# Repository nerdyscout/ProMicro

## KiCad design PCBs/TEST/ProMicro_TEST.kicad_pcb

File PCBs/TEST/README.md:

# ProMicro_TEST
This module can be mounted to an [Arduino Pro Mini](https://www.sparkfun.com/products/11113), [Arduino Nano](https://store.arduino.cc/arduino-nano), [Sparkfun Pro Micro](https://www.sparkfun.com/products/12587), or any other pincompatible MCU running with 3.3V.

## Documentation
All files can be found on [Github](https://github.com/nerdyscout/ProMicro_TEST).

### Schematic

### Layout

### BoM
  * [interactiveHTMLBoM](https://nerdyscout.github.io/ProMicro_TEST/docs/BOM/ProMicro_TEST.html)
  * [kicost](docs/BOM/ProMicro_TEST.xlsx)
  * [csv](docs/BOM/ProMicro_TEST.csv)

## Gerbers
can be found within the Github [repository](https://github.com/nerdyscout/ProMicro_TEST/tree/master/gerbers).

## Code
| | TEST1 | TEST2 |
| --- | --- | --- |
| Arduino Nano | tbd | [TEST](examples/Arduino_Nano_TEST/Arduino_Nano_TEST.ino) |
| Sparkfun ProMicro | [TEST](examples/Sparkfun_ProMicro_TEST/Sparkfun_ProMicro_TEST.ino) | [TEST](examples/Sparkfun_ProMicro_TEST/Sparkfun_ProMicro_TEST.ino) |

## Links
  * [hackaday.io](https://hackaday.io/project/171898-promicro)

## License
Copyright Stefan Herold 2020

This documentation describes Open Hardware and is licensed under the CERN OHL v.1.2.

You may redistribute and modify this documentation under the terms of the CERN OHL v.1.2. (http://ohwr.org/cernohl). This documentation is distributed WITHOUT ANY EXPRESS OR IMPLIED WARRANTY, INCLUDING OF MERCHANTABILITY, SATISFACTORY QUALITY AND FITNESS FOR A PARTICULAR PURPOSE. Please see the CERN OHL v.1.2 for applicable conditions

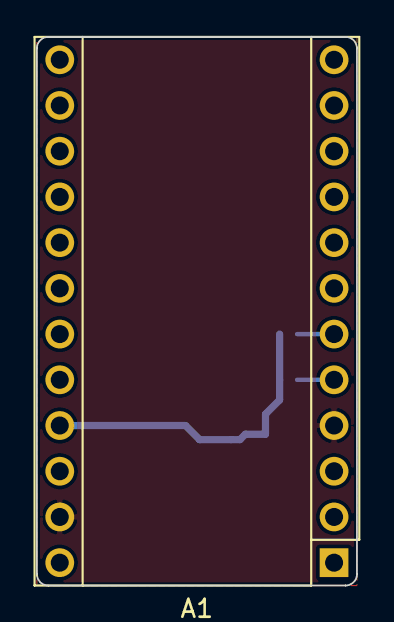
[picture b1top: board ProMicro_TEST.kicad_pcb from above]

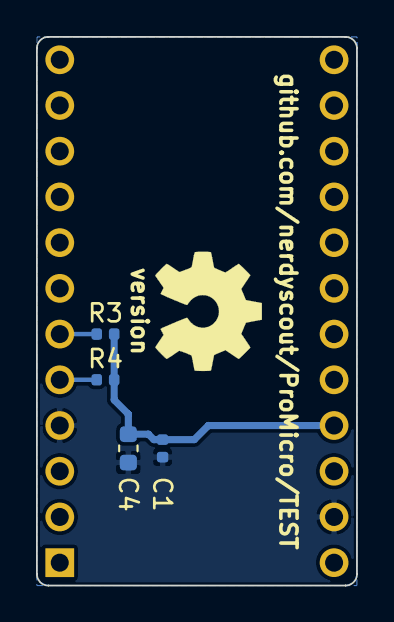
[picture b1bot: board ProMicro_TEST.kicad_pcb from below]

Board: 2 copper layers, 17.8 x 30.5 mm, 6 parts (5 on the bottom side), 4 nets.

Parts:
A1: Sparkfun_Pro_Micro_3V3; Sparkfun_Pro_Micro
C1: 100n; C_0402_1005Metric
C4: 10µ; C_0603_1608Metric
LOGO1: Logo_Open_Hardware_Small; OSHW-Symbol_6.7x6mm_SilkScreen
R3, R4: 4k7; R_0402_1005Metric

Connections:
+3V3: A1.21, C1.1, C4.1, R3.2, R4.2
GND: A1.4, A1.23, C1.2, C4.2
SCL: A1.6, R3.1
SDA: A1.5, R4.1

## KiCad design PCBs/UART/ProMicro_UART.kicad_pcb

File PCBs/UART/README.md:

:warning: **do not use this design** it does contain some bad footprints! 

# ProMicro_UART
USB to Serial, SPI, I2C or JTAG

## Documentation
All files can be found on [Github](https://github.com/nerdyscout/ProMicro_UART).

### Schematic

### Layout

### BoM
  * [interactiveHTMLBoM](https://nerdyscout.github.io/ProMicro_UART/docs/bom/ibom.html)
  * [kicost](docs/bom/ProMicro_UART.xlsx)
  * [csv](docs/bom/ProMicro_UART.csv)

## Gerbers
can be found within the Github [repository](gerbers).

## Links
  * [hackaday.io](https://hackaday.io/project/171898-promicro)

## License
Copyright Stefan Herold 2020

This documentation describes Open Hardware and is licensed under the CERN OHL v.1.2.

You may redistribute and modify this documentation under the terms of the CERN OHL v.1.2. (http://ohwr.org/cernohl). This documentation is distributed WITHOUT ANY EXPRESS OR IMPLIED WARRANTY, INCLUDING OF MERCHANTABILITY, SATISFACTORY QUALITY AND FITNESS FOR A PARTICULAR PURPOSE. Please see the CERN OHL v.1.2 for applicable conditions

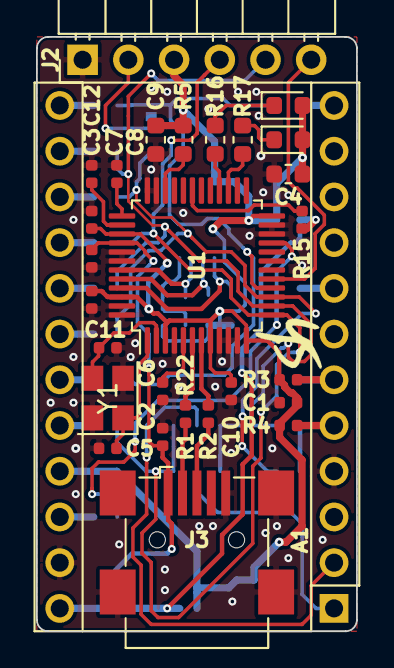
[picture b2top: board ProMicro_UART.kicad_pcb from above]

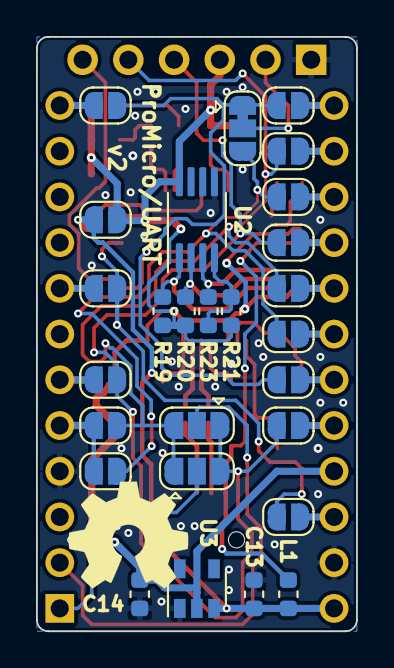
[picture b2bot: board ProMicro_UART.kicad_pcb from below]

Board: 2 copper layers, 17.8 x 33.0 mm, 57 parts (28 on the bottom side), 45 nets.

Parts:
A1: Sparkfun_Pro_Micro_3V3; Sparkfun_Pro_Micro
C1, C3, C7, C8, C10, C11, C12: 100n; C_0402_1005Metric
C2: 4.7µ; C_0402_1005Metric
C4: 10µ; C_0603_1608Metric
C5, C6: 27p; C_0402_1005Metric
C9: 4.7µ; R_0603_1608Metric
C13, C14: 1µ; C_0603_1608Metric
D1: TX; LED_0603_1608Metric
D2: RX; LED_0603_1608Metric
J2: Conn_01x06; PinHeader_1x06_P2.54mm_Horizontal
J3: USB_B_Mini; USB_Mini-B_Wuerth_65100516121_Horizontal
JP1, JP2, JP3, JP4, JP5, JP6, JP7, JP8, JP9, JP12, JP13, JP14, JP15, JP17, JP18: Jumper_NO_Small; SolderJumper-2_P1.3mm_Open_RoundedPad1.0x1.5mm
JP10, JP11: Jumper_3_Bridged12; SolderJumper-3_P1.3mm_Open_RoundedPad1.0x1.5mm
JP16: Jumper_3_Bridged12; SolderJumper-3_P1.3mm_Bridged12_RoundedPad1.0x1.5mm
L1: 0; L_0603_1608Metric
LOGO1: Logo_Open_Hardware_Small; OSHW-Symbol_6.7x6mm_SilkScreen
R1, R2: 22; R_0402_1005Metric
R3, R4: 4k7; R_0402_1005Metric
R5: 1k; R_0603_1608Metric
R15: 39k; R_0402_1005Metric
R16, R17: 220; R_0603_1608Metric
R19, R20, R21: 10k; R_0603_1608Metric
R22: 12k; R_0402_1005Metric
R23: 2k; R_0603_1608Metric
TP1: initials
U1: FT232H; LQFP-48_7x7mm_P0.5mm
U2: 93CxxB; MSOP-8_3x3mm_P0.65mm
U3: AZ1117-3.3; SOT-23-5
Y1: 12MHz; Crystal_SMD_3225-4Pin_3.2x2.5mm

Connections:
+3V3: A1.21, C1.1, C4.1, C9.1, C10.2, C11.2, C12.1, C14.1, D1.2, D2.2, J2.3, JP18.2, R3.2, R4.2, R5.2, R19.2, R20.2, R21.2, U1.3, U1.8, U1.12, U1.24, U1.39, U1.46, U2.8, U3.2
+5V: A1.24, C13.1, JP18.1, L1.1, R15.2, U3.3
/EECLK: R20.1, U1.44, U2.2
/EECS: R19.1, U1.45, U2.1
/EEDAT: R23.1, U1.43, U2.3
A0: A1.17, JP7.2
A1: A1.18, JP8.2
A2: A1.19, JP9.2
A3: A1.20, JP6.2
ACBUS0: JP12.1, JP17.1, U1.21
ADBUS0: J2.4, JP1.1, JP6.1, JP10.3, JP11.1, JP15.1, U1.13
ADBUS1: J2.5, JP2.1, JP7.1, JP10.1, JP11.3, JP13.1, U1.14
ADBUS2: JP3.1, JP8.1, JP14.1, JP16.3, U1.15
ADBUS3: JP4.1, JP5.1, JP9.1, JP16.1, U1.16
ADBUS4: J2.6, U1.17
D0: A1.2, JP11.2
D1: A1.1, JP10.2
D2: A1.5, JP13.2, JP14.2, R4.1
D3: A1.6, JP15.2, R3.1
D5: A1.8, JP12.2
D9: A1.12, JP4.2
D10: A1.13, JP5.2
D14: A1.15, JP3.2
D15: A1.16, JP1.2
D16: A1.14, JP2.2
GND: A1.4, A1.23, C1.2, C2.2, C3.2, C4.2, C5.2, C6.2, C7.2, C8.2, C9.2, C10.1, C11.1, C12.2, C13.2, C14.2, J2.1, J3.5, J3.6, R22.2, U1.4, U1.9, U1.10, U1.11, U1.22, U1.23, U1.35, U1.36, U1.41, U1.42, U1.47, U1.48, U2.5, U3.1, Y1.2, Y1.4
unnamed: C2.1, C3.1, J3.1, L1.2, U1.40
unnamed: C5.1, U1.1, Y1.1
unnamed: C6.1, U1.2, Y1.3
unnamed: C7.1, U1.38
unnamed: C8.1, U1.37
unnamed: D1.1, R16.2
unnamed: D2.1, R17.2
unnamed: J2.2, JP16.2
unnamed: J3.2, R1.2
unnamed: J3.3, R2.2
unnamed: R1.1, U1.6
unnamed: R2.1, U1.7
unnamed: R5.1, U1.34
unnamed: R21.1, R23.2, U2.4
unnamed: R22.1, U1.5
PWRSAV: R15.1, U1.31
RXLED: R17.1, U1.27
Reset: A1.22, JP17.2
TXLED: R16.1, U1.28

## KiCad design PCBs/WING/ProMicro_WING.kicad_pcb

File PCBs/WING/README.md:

---
layout: docu
title: ProMicro_WING
subtitle: Adafruit Feather WING Adapter
---

## Documents

### Schematic

### Layout

---

## Bill of Materials
* [interactivBOM](https://nerdyscout.github.io/ProMicro_CONN/docs/bom/ProMicro_WING.html))
* [csv](docs/bom/ProMicro_WING.csv)
* [KiBoM](docs/bom/ProMicro_WING.xlsx)

---

## Compatibility

| Board | ModTEMP | CanTEMP | 
| --- | --- | --- | 
| [Arduino Pro Mini 328 - 5V/16MHz](https://www.sparkfun.com/products/11113) | yes | 
| [Arduino Pro Mini 328 - 3.3V/8MHz](https://www.sparkfun.com/products/11114) | yes | 
| [Sparkfun ProMicro 3.3V@8MHz](https://www.sparkfun.com/products/12587) | yes |
| [Sparkfun ProMicro 5V@16MHz](https://www.sparkfun.com/products/12640) | yes |
| [SparkFun Qwiic Pro Micro USB-C](https://www.sparkfun.com/products/15795) | yes |

**Warning:**
As I am not able to test all boards this compatibility list is just an estimation.
{: .alert .alert-danger}

---

## License
Copyright Stefan Herold 2020

This documentation describes Open Hardware and is licensed under the CERN OHL v.1.2.

You may redistribute and modify this documentation under the terms of the CERN OHL v.1.2. (http://ohwr.org/cernohl). This documentation is distributed WITHOUT ANY EXPRESS OR IMPLIED WARRANTY, INCLUDING OF MERCHANTABILITY, SATISFACTORY QUALITY AND FITNESS FOR A PARTICULAR PURPOSE. Please see the CERN OHL v.1.2 for applicable conditions

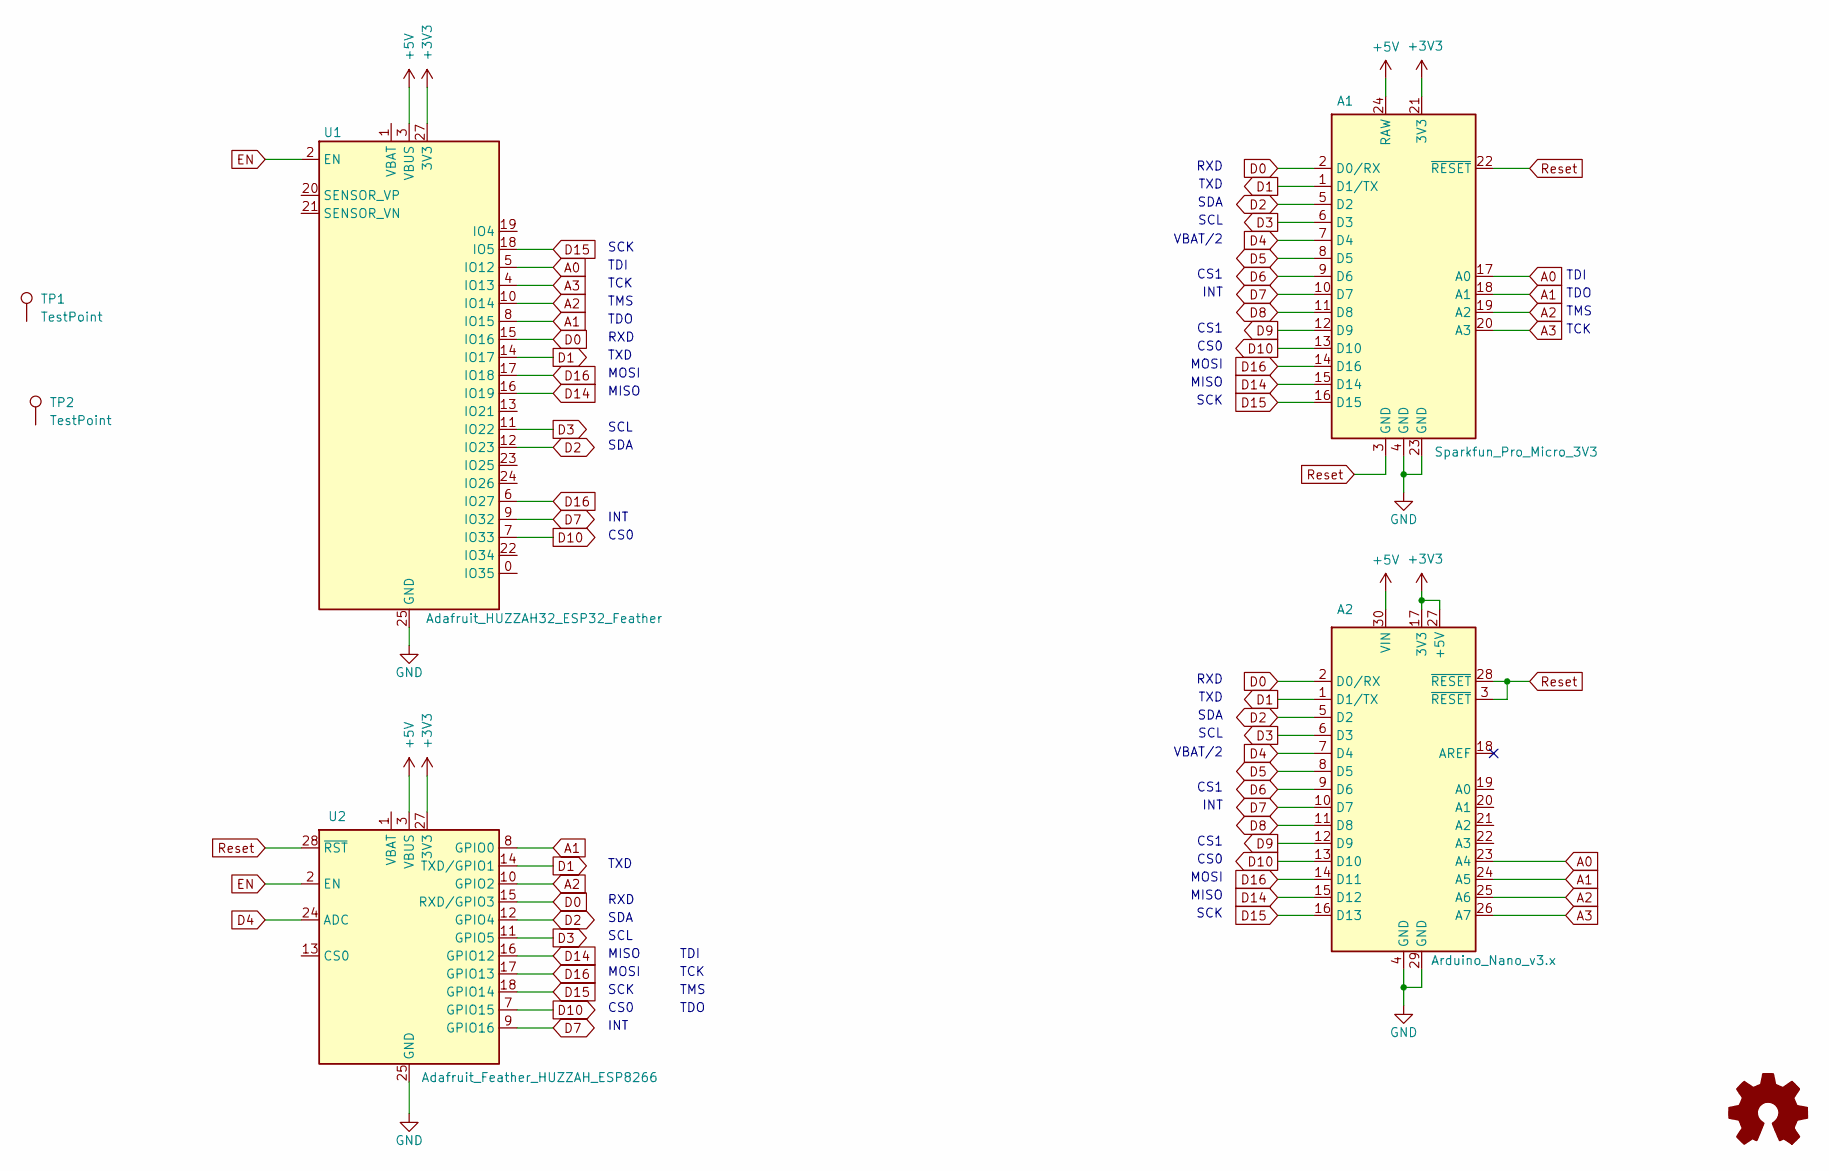
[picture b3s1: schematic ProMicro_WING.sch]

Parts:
A1: Sparkfun_Pro_Micro_3V3; Sparkfun_Pro_Micro
A2: Arduino_Nano_v3.x; Arduino_Nano_mod
LOGO1: Logo_Open_Hardware_Small; OSHW-Symbol_6.7x6mm_SilkScreen
TP1, TP2: TestPoint; MountingHole_2.7mm
U1: Adafruit_HUZZAH32_ESP32_Feather; Adafruit_Feather_mod2
U2: Adafruit_Feather_HUZZAH_ESP8266; Adafruit_Feather

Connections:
+3V3: A1.21 (3V3), A2.17 (3V3), A2.27 (+5V), U1.27 (3V3), U2.27 (3V3)
+5V: A1.24 (RAW), A2.30 (VIN), U1.3 (VBUS), U2.3 (VBUS)
A0: A1.17 (A0), A2.23 (A4), U1.5 (IO12)
A1: A1.18 (A1), A2.24 (A5), U1.8 (IO15), U2.8 (GPIO0)
A2: A1.19 (A2), A2.25 (A6), U1.10 (IO14), U2.10 (GPIO2)
A3: A1.20 (A3), A2.26 (A7), U1.4 (IO13)
D0: A1.2 (D0/RX), A2.2 (D0/RX), U1.15 (IO16), U2.15 (RXD/GPIO3)
D1: A1.1 (D1/TX), A2.1 (D1/TX), U1.14 (IO17), U2.14 (TXD/GPIO1)
D2: A1.5 (D2), A2.5 (D2), U1.12 (IO23), U2.12 (GPIO4)
D3: A1.6 (D3), A2.6 (D3), U1.11 (IO22), U2.11 (GPIO5)
D4: A1.7 (D4), A2.7 (D4), U2.24 (ADC)
D5: A1.8 (D5), A2.8 (D5)
D6: A1.9 (D6), A2.9 (D6)
D7: A1.10 (D7), A2.10 (D7), U1.9 (IO32), U2.9 (GPIO16)
D8: A1.11 (D8), A2.11 (D8)
D9: A1.12 (D9), A2.12 (D9)
D10: A1.13 (D10), A2.13 (D10), U1.7 (IO33), U2.7 (GPIO15)
D14: A1.15 (D14), A2.15 (D12), U1.16 (IO19), U2.16 (GPIO12)
D15: A1.16 (D15), A2.16 (D13), U1.18 (IO5), U2.18 (GPIO14)
D16: A1.14 (D16), A2.14 (D11), U1.6 (IO27), U1.17 (IO18), U2.17 (GPIO13)
EN: U1.2 (EN), U2.2 (EN)
GND: A1.4 (GND), A1.23 (GND), A2.4 (GND), A2.29 (GND), U1.25 (GND), U2.25 (GND)
Reset: A1.3 (GND), A1.22 (~RESET), A2.3 (~RESET), A2.28 (~RESET), U2.28 (~RST)

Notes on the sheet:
VBAT/2
CS1
TDI
TDO
RXD
TXD
SDA
SCL
INT
CS0
MOSI
MISO
SCK
TMS
TCK

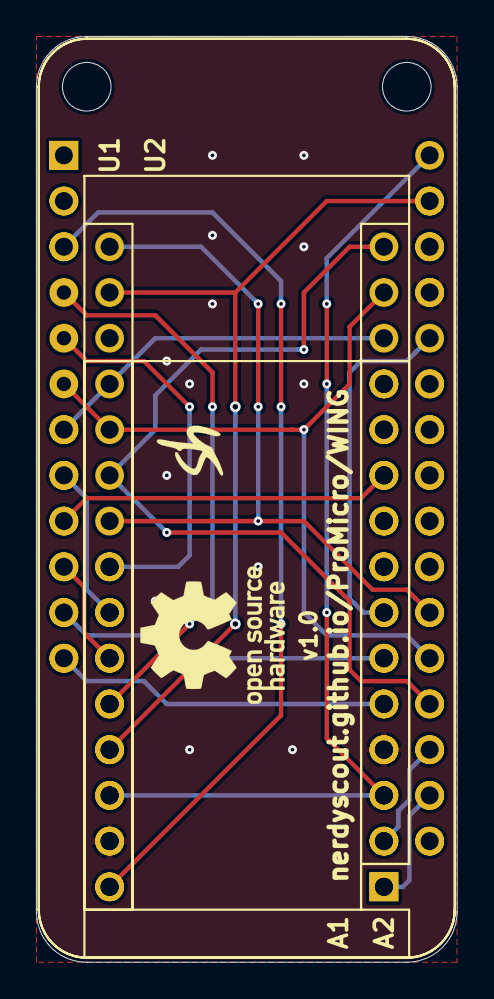
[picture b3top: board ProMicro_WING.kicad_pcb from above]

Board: 2 copper layers, 23.4 x 51.4 mm, 8 parts (0 on the bottom side), 23 nets.

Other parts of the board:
TP3: initials

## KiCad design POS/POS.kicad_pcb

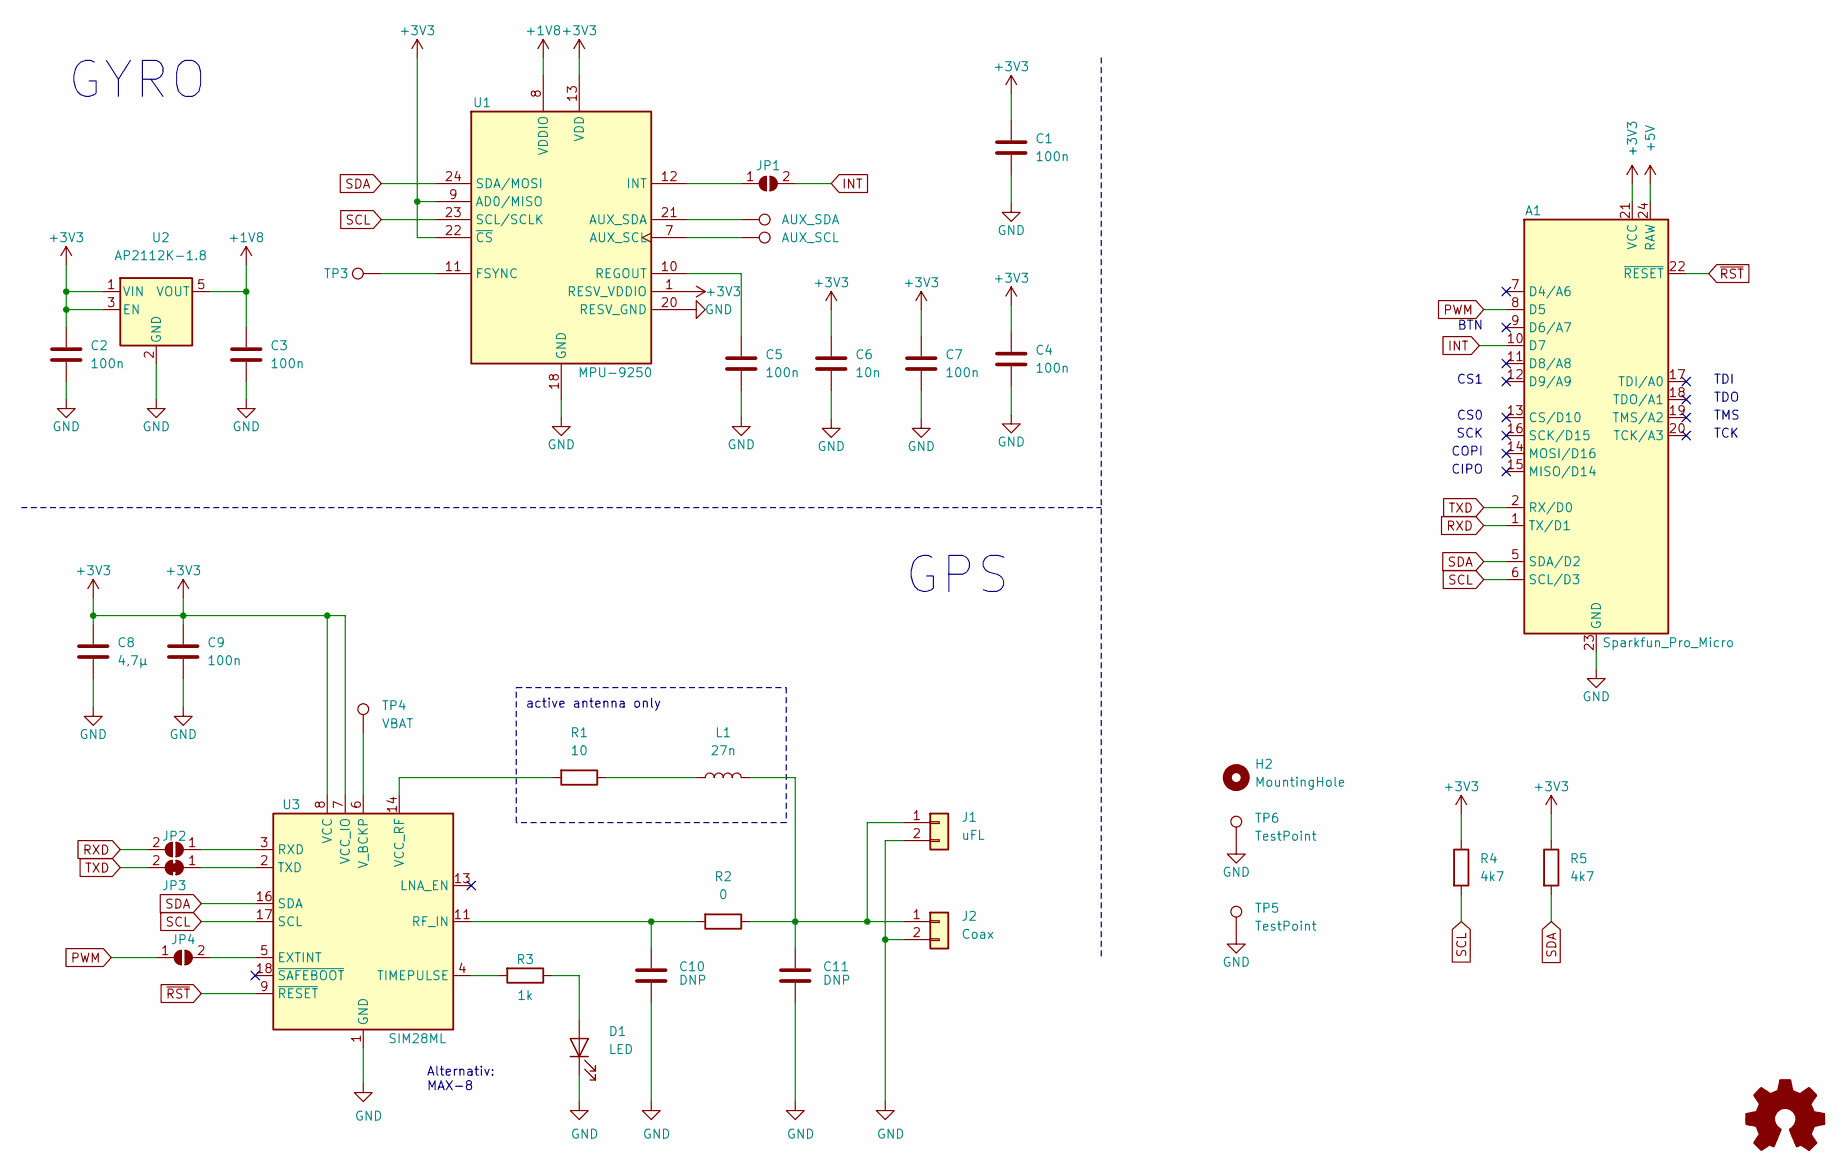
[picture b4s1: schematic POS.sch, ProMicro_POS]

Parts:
A1: Sparkfun_Pro_Micro
C1: 100n; C_0402_1005Metric; MPN CL05B103KB5NNNC; LCSC# C15195
C2, C3, C4, C5, C7, C9: 100n; C_0402_1005Metric; MPN CL05B104KO5NNNC; LCSC# C1525
C6: 10n; C_0402_1005Metric; MPN CL05B103KB5NNNC; LCSC# C15195
C8: 4,7µ; C_0603_1608Metric; MPN CL10A475KO8NNNC; LCSC# C19666
C10, C11: DNP; C_0402_1005Metric
D1: LED; LED_0603_1608Metric; MPN 19-217/BHC-ZL1M2RY/3T; LCSC# C72041
H2: MountingHole; MountingHole_2.1mm
J1: uFL; U.FL_Hirose_U.FL-R-SMT-1_Vertical
J2: Coax; SMA_Samtec_SMA-J-P-H-ST-EM1_EdgeMount
JP1, JP4: SolderJumper_2_Open; SolderJumper-2_P1.3mm_Open_RoundedPad1.0x1.5mm
JP2: Jumper_NO_Small; SolderJumper-2_P1.3mm_Open_RoundedPad1.0x1.5mm
JP3: Jumper_NC_Small; SolderJumper-2_P1.3mm_Bridged_RoundedPad1.0x1.5mm
L1: 27n; L_0402_1005Metric
LOGO1: Logo_Open_Hardware_Small; OSHW-Symbol_6.7x6mm_SilkScreen
R1: 10; R_0402_1005Metric
R2: 0; R_0402_1005Metric; MPN 0402WGF0000TCE; LCSC# C17168
R3: 1k; R_0402_1005Metric; MPN 0402WGF1001TCE; LCSC# C11702
R4, R5: 4k7; R_0402_1005Metric; MPN 0402WGF4701TCE; LCSC# C25900
TP1: AUX_SDA; TestPoint_Pad_D1.5mm
TP2: AUX_SCL; TestPoint_Pad_D1.5mm
TP3: FSYNC; TestPoint_Pad_D1.5mm
TP4: VBAT; TestPoint_THTPad_D1.5mm_Drill0.7mm
TP5, TP6: TestPoint; TestPoint_Pad_1.5x1.5mm
U1: MPU-9250; InvenSense_QFN-24_3x3mm_P0.4mm; MPN MPU-9250; LCSC# C71459
U2: AP2112K-1.8; SOT-23-5
U3: SIM28ML; ublox_MAX; MPN MAX-8C-0-10

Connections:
+1V8: C3.1, U1.8 (VDDIO), U2.5 (VOUT)
+3V3: A1.21 (VCC), C1.1, C2.1, C4.1, C6.1, C7.1, C8.1, C9.1, R4.1, R5.1, U1.1 (RESV_VDDIO), U1.9 (AD0/MISO), U1.13 (VDD), U1.22 (~CS), U2.1 (VIN), U2.3 (EN), U3.7 (VCC_IO), U3.8 (VCC)
+5V: A1.24 (RAW)
GND: A1.3 (GND), A1.4 (GND), A1.23 (GND), C1.2, C2.2, C3.2, C4.2, C5.2, C6.2, C7.2, C8.2, C9.2, C10.2, C11.2, D1.1 (K), J1.2, J2.2, TP5.1, TP6.1, U1.18 (GND), U1.20 (RESV_GND), U2.2 (GND), U3.1 (GND), U3.10 (GND), U3.12 (GND)
INT: A1.10 (D7), JP1.2 (B)
unnamed: C5.1, U1.10 (REGOUT)
unnamed: C10.1, R2.2, U3.11 (RF_IN)
unnamed: C11.1, J1.1, J2.1, L1.2, R2.1
unnamed: D1.2 (A), R3.1
unnamed: JP1.1 (A), U1.12 (INT)
unnamed: JP2.1 (A), U3.3 (RXD)
unnamed: JP3.1 (A), U3.2 (TXD)
unnamed: JP4.2 (B), U3.5 (EXTINT)
unnamed: L1.1, R1.1
unnamed: R1.2, U3.14 (VCC_RF)
unnamed: R3.2, U3.4 (TIMEPULSE)
unnamed: TP1.1, U1.21 (AUX_SDA)
unnamed: TP2.1, U1.7 (AUX_SCL)
unnamed: TP3.1, U1.11 (FSYNC)
unnamed: TP4.1, U3.6 (V_BCKP)
PWM: A1.8 (D5), JP4.1 (A)
RXD: A1.1 (TX/D1), JP2.2 (B)
SCL: A1.6 (SCL/D3), R4.2, U1.23 (SCL/SCLK), U3.17 (SCL)
SDA: A1.5 (SDA/D2), R5.2, U1.24 (SDA/MOSI), U3.16 (SDA)
TXD: A1.2 (RX/D0), JP3.2 (B)
~RST: A1.22 (~RESET), U3.9 (~RESET)

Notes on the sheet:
GYRO
GPS
active antenna only
Alternativ: MAX-8
TDI
TDO
TMS
TCK
SCK
CIPO
COPI
CS0
CS1
BTN

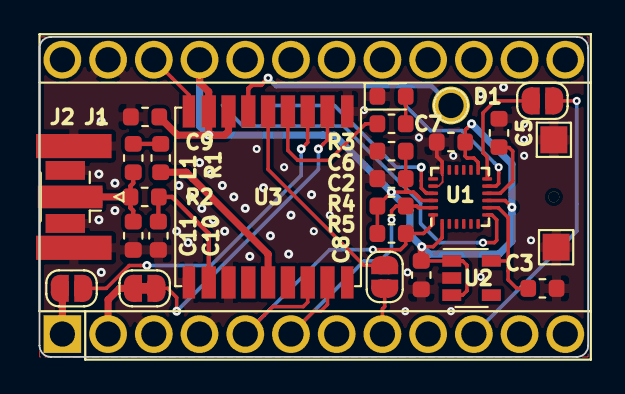
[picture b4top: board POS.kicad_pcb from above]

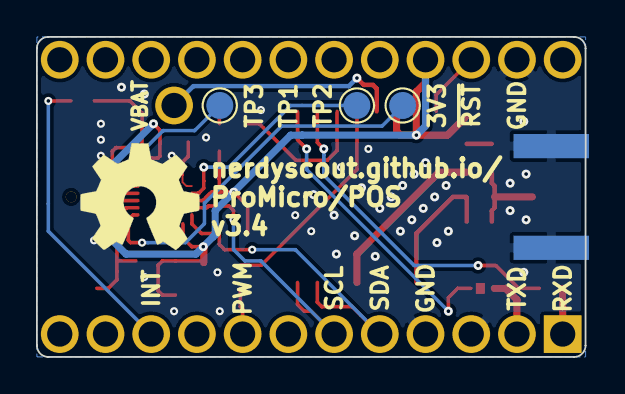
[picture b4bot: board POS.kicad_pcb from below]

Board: 4 copper layers, 30.5 x 17.8 mm, 34 parts (4 on the bottom side), 25 nets.

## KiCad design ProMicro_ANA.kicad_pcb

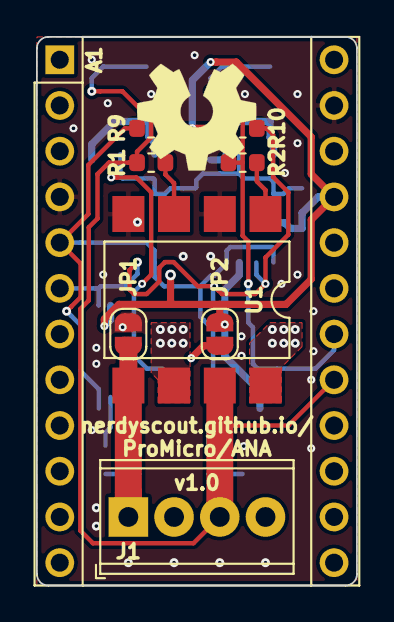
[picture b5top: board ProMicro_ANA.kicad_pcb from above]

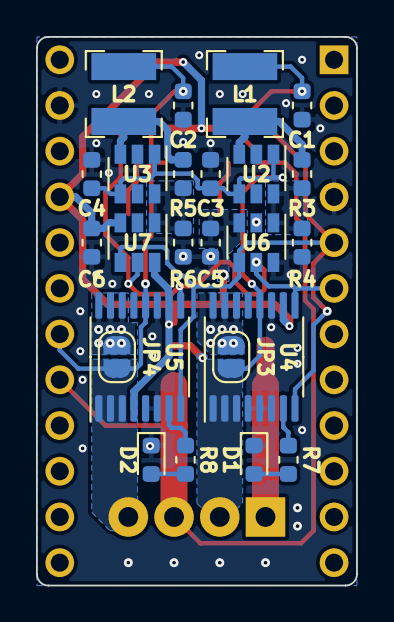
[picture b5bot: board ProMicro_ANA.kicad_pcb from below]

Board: 2 copper layers, 17.8 x 30.5 mm, 34 parts (24 on the bottom side), 20 nets.

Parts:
A1: Sparkfun_Pro_Micro_3V3; Sparkfun_Pro_Micro
C1, C2: 10µ; C_0603_1608Metric
C3, C4: 4.7µ; C_0603_1608Metric
C5, C6: 100nF; C_0603_1608Metric
D1, D2: LED; LED_0603_1608Metric
J1: Conn_01x04; TerminalBlock_Phoenix_MPT-0,5-4-2.54_1x04_P2.54mm_Horizontal
JP1, JP2, JP3, JP4: Jumper_NO_Small; SolderJumper-2_P1.3mm_Open_RoundedPad1.0x1.5mm
L1, L2: 2.2µ; L_Bourns-SRN4018
LOGO1: Logo_Open_Hardware_Small; OSHW-Symbol_6.7x6mm_SilkScreen
R1, R2, R7, R8: 220; R_0603_1608Metric
R3, R5: 200k; R_0603_1608Metric
R4, R6: 47k; R_0603_1608Metric
R9, R10: 4k7; R_0603_1608Metric
U1: LTV-827S; SMDIP-8_W9.53mm
U2, U3: TLV62569DDC; SOT-23-6
U4, U5: INA260; TSSOP-16_4.4x5mm_P0.65mm
U6, U7: MCP4725xxx-xCH; SOT-23-6

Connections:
+3V3: A1.21, C5.1, C6.1, JP2.2, R9.2, R10.2, U4.10, U5.4, U5.10, U6.3, U7.3, U7.6
A0: A1.17, C1.1, J1.3, L1.1, R1.2, U1.7
A1: A1.18, C2.1, J1.4, JP4.1, L2.1, R2.2, U5.1, U5.2, U5.3, U5.12
D2: A1.5, R9.1, U4.8, U5.8, U6.4, U7.4
D3: A1.6, R10.1, U4.9, U5.9, U6.5, U7.5
GND: A1.4, A1.23, C1.2, C2.2, C3.2, C4.2, C5.2, C6.2, D1.1, D2.1, JP1.2, R4.1, R6.1, U1.2, U1.4, U2.2, U3.2, U4.4, U4.5, U4.6, U4.11, U5.5, U5.6, U5.11, U6.2, U6.6, U7.2
unnamed: C3.1, C4.1, J1.2, JP2.1, JP3.1, U2.1, U2.4, U3.1, U3.4, U4.1, U4.2, U4.3, U4.12
unnamed: D1.2, R7.1
unnamed: D2.2, R8.1
unnamed: J1.1, JP1.1, U1.5
unnamed: JP3.2, U1.6, U4.14, U4.15, U4.16
unnamed: JP4.2, U1.8, U5.14, U5.15, U5.16
unnamed: L1.2, R3.2, U2.3
unnamed: L2.2, R5.2, U3.3
unnamed: R1.1, U1.3
unnamed: R2.1, U1.1
unnamed: R3.1, R4.2, U2.6, U6.1
unnamed: R5.1, R6.2, U3.6, U7.1
unnamed: R7.2, U4.7
unnamed: R8.2, U5.7

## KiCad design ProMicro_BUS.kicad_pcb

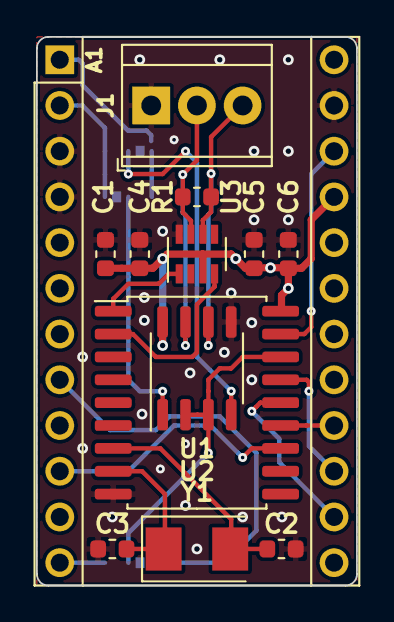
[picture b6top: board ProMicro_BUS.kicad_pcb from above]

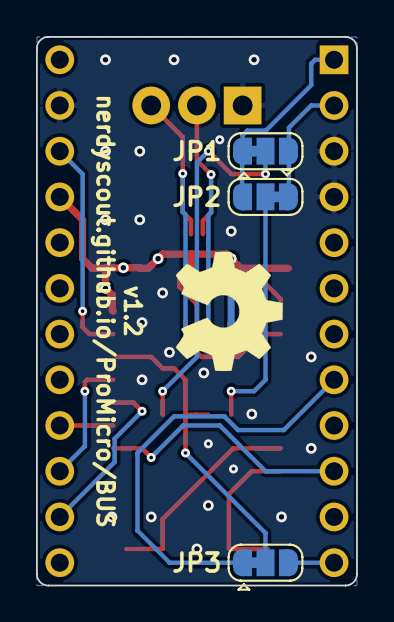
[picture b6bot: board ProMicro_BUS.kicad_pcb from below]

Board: 2 copper layers, 17.8 x 30.5 mm, 17 parts (4 on the bottom side), 20 nets.

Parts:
A1: Sparkfun_Pro_Micro_3V3; Sparkfun_Pro_Micro
C1, C5, C6: 100n; C_0603_1608Metric
C2, C3: C; C_0603_1608Metric
C4: 10µ; C_0603_1608Metric
J1: Conn_01x03; TerminalBlock_TE_282834-3_1x03_P2.54mm_Horizontal
JP1, JP2, JP3: SolderJumper_3_Bridged12; SolderJumper-3_P1.3mm_Bridged12_RoundedPad1.0x1.5mm
LOGO1: Logo_Open_Hardware_Small; OSHW-Symbol_6.7x6mm_SilkScreen
R1: 120; R_0603_1608Metric
U1: MAX3483; SO-8_3.9x4.9mm_P1.27mm
U2: MCP2515-xSO; SOIC-18W_7.5x11.6mm_P1.27mm
U3: MAX3051; SOT-23-8
Y1: Crystal; Crystal_SMD_5032-2Pin_5.0x3.2mm

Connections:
+3V3: A1.21, C1.1, C4.1, C5.1, C6.1, U1.8, U2.18, U3.3
/A: J1.3, R1.2, U1.6, U3.6
/B: J1.2, R1.1, U1.7, U3.7
CS: JP3.2, U1.2, U1.3, U2.16
D0: A1.2, JP1.3, JP2.1
D1: A1.1, JP1.1, JP2.3
D5: A1.8, JP3.1
D7: A1.10, U2.12
D9: A1.12, JP3.3
D14: A1.15, U2.15
D15: A1.16, U2.13
D16: A1.14, U2.14
GND: A1.3, A1.4, A1.23, C1.2, C2.1, C3.2, C4.2, C5.2, C6.2, J1.1, U1.5, U2.9, U3.2, U3.8
unnamed: C2.2, U2.7, Y1.2
unnamed: C3.1, U2.8, Y1.1
unnamed: JP1.2, U1.4
unnamed: JP2.2, U1.1
unnamed: U2.1, U3.1
unnamed: U2.2, U3.4
Reset: A1.22, U2.17

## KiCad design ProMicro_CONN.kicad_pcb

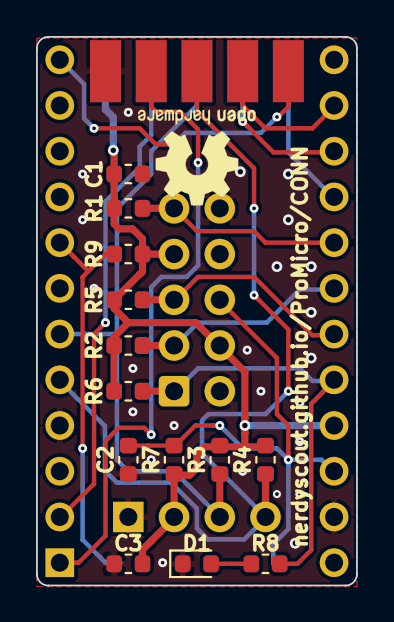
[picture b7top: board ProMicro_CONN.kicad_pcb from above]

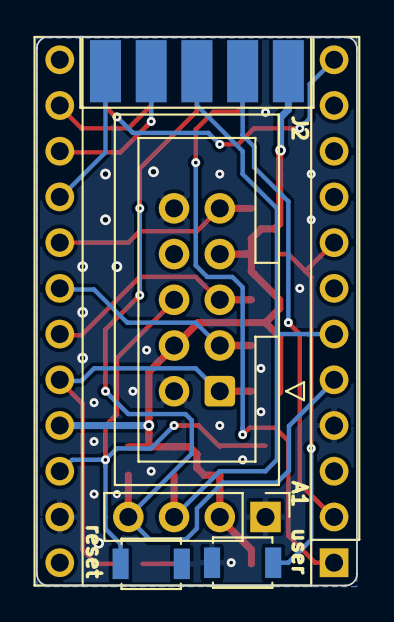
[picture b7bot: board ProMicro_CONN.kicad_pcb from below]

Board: 2 copper layers, 17.8 x 30.5 mm, 20 parts (6 on the bottom side), 17 nets.

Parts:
A1: Sparkfun_Pro_Micro_3V3; Sparkfun_Pro_Micro
C1, C2: 1µ; C_0603_1608Metric
C3: 100n; C_0603_1608Metric
D1: LED; LED_0603_1608Metric
J1: AVR-JTAG-10; IDC-Header_2x05_P2.54mm_Vertical
J2: UEXT_Host; UEXT
J3: Display; PinHeader_1x04_P2.54mm_Vertical
LOGO1: Logo_Open_Hardware_Small; OSHW-Logo2_7.3x6mm_SilkScreen
R1, R2, R3, R4, R5, R6, R7, R9: 4k7; R_0603_1608Metric
R8: 1k; R_0603_1608Metric
SW1: reset; SW_SPST_B3U-1000P
SW2: user; SW_SPST_B3U-1000P

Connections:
+3V3: A1.21, C1.1, C3.1, J1.4, J1.7, J2.1, J3.2, R1.2, R2.2, R3.2, R4.2, R5.2, R6.2, R7.2, R9.2
A0: A1.17, J1.9, R1.1
A1: A1.18, J1.3, R2.1
A2: A1.19, J1.5, R5.1
A3: A1.20, J1.1, R6.1, R8.2
D0: A1.2, J2.3
D1: A1.1, J2.4
D2: A1.5, J2.6, J3.4, R4.1
D3: A1.6, J2.5, J3.3, R3.1
D5: A1.8, R9.1, SW2.2
D9: A1.12, J2.10
D14: A1.15, J2.7
D15: A1.16, J2.9
D16: A1.14, J2.8
GND: A1.4, A1.23, C1.2, C2.2, C3.2, D1.1, J1.2, J1.10, J2.2, J3.1, SW1.1, SW2.1
unnamed: D1.2, R8.1
Reset: A1.22, C2.1, J1.6, R7.1, SW1.2

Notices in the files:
PCBs/TEST/ProMicro_TEST.kicad_pcb:
CERN Open Hardware Licence v1.2
